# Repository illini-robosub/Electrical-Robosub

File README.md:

The RoboSub PCB components 

For now just power distribution board

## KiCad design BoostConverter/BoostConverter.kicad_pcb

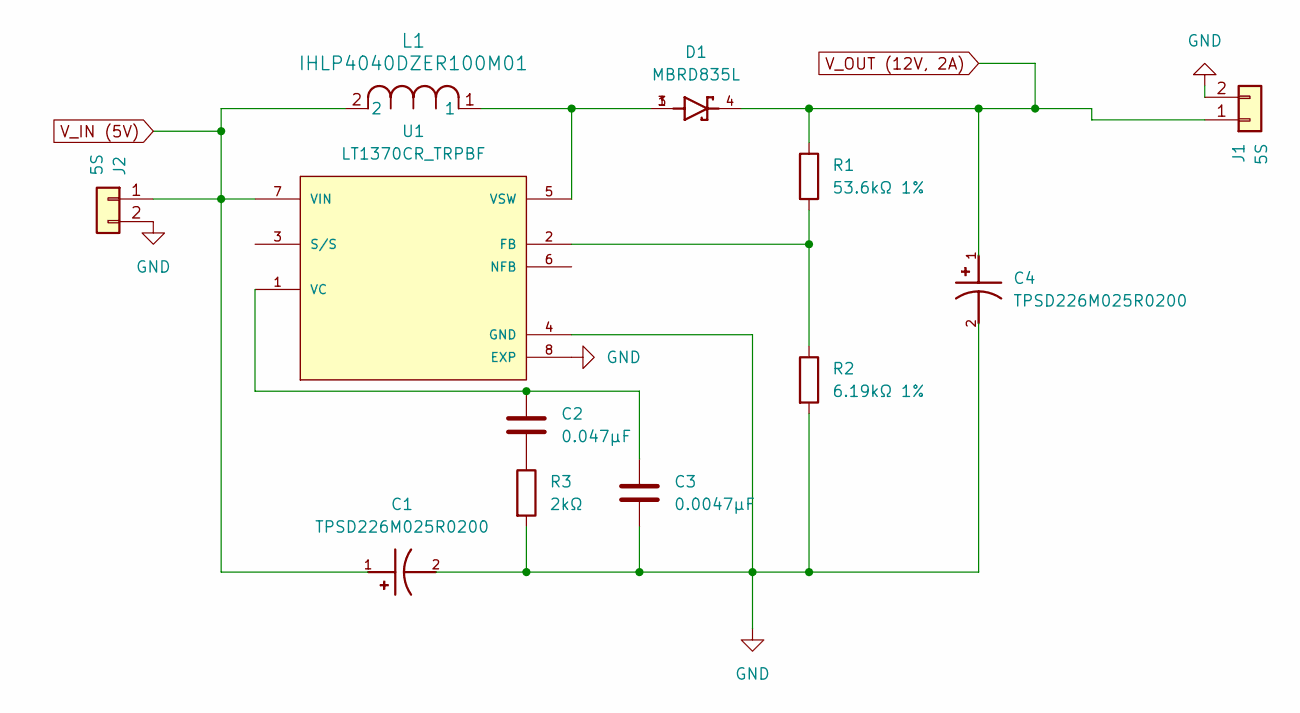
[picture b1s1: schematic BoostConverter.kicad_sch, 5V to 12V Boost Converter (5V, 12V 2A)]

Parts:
C1, C4: TPSD226M025R0200; CP_EIA-7343-30_AVX-N; PARTREV N/A
C2: 0.047µF; C_0603_1608Metric
C3: 0.0047µF; C_0603_1608Metric
D1: MBRD835L; TO-252-3_TabPin4; PARTREV 8
J1, J2: 5S; TerminalBlock_MetzConnect_Type086_RT03403HBLC_1x03_P3.81mm_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
L1: IHLP4040DZER100M01; L_Vishay_IHLP-4040
R1: 53.6kΩ 1%; R_0603_1608Metric
R2: 6.19kΩ 1%; R_0603_1608Metric
R3: 2kΩ; R_0603_1608Metric
U1: LT1370CR_TRPBF; TO-263-7_TabPin8

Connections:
GND: C1.2, C3.2, C4.2, J1.2, J2.2, R2.2, R3.2, U1.4 (GND), U1.8 (EXP)
unnamed: C2.2, R3.1
unnamed: R1.2, R2.1, U1.2 (FB)
unnamed: C2.1, C3.1, U1.1 (VC)
unnamed: D1.1, D1.3, L1.1, U1.5 (VSW)
V_IN (5V): C1.1, J2.1, L1.2, U1.7 (VIN)
V_OUT (12V, 2A): C4.1, D1.2, D1.4, J1.1, R1.1

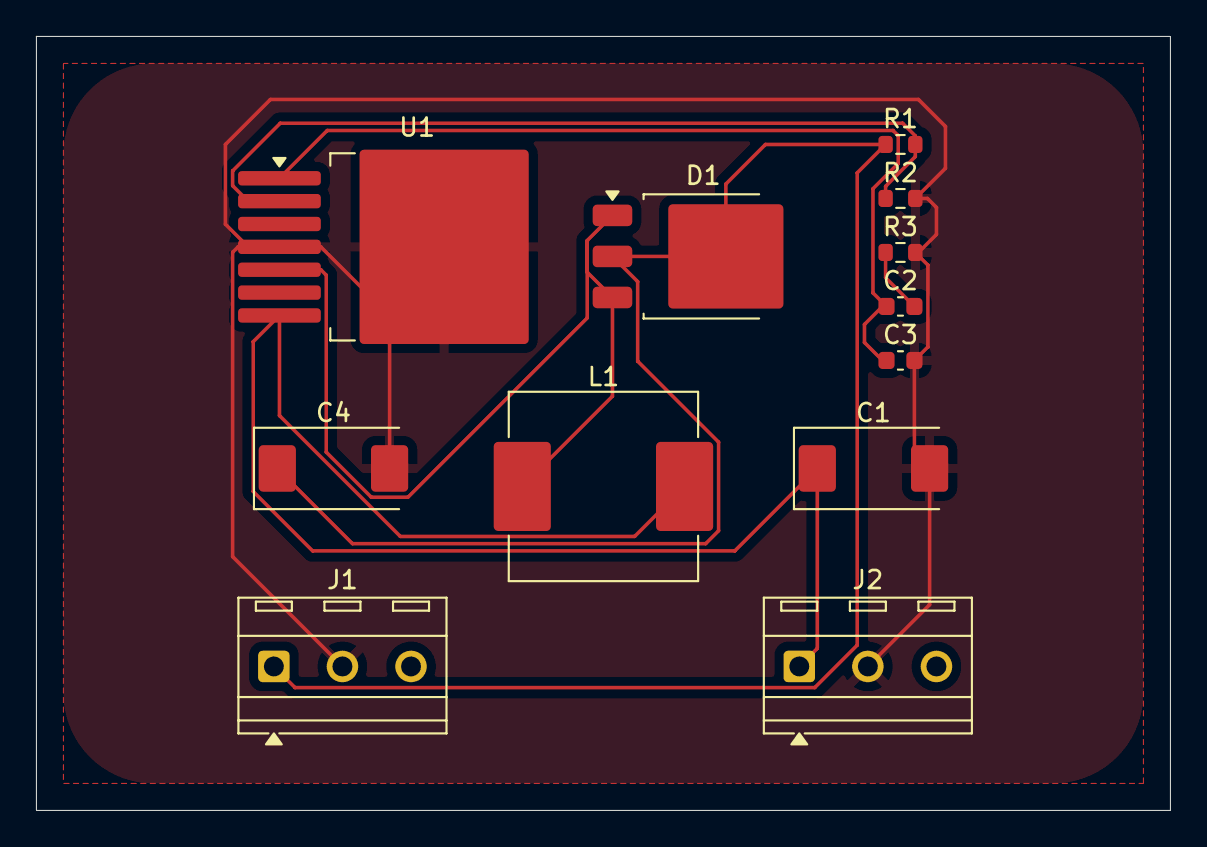
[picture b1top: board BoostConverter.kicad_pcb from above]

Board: 2 copper layers, 63.0 x 43.0 mm, 12 parts (0 on the bottom side), 7 nets.

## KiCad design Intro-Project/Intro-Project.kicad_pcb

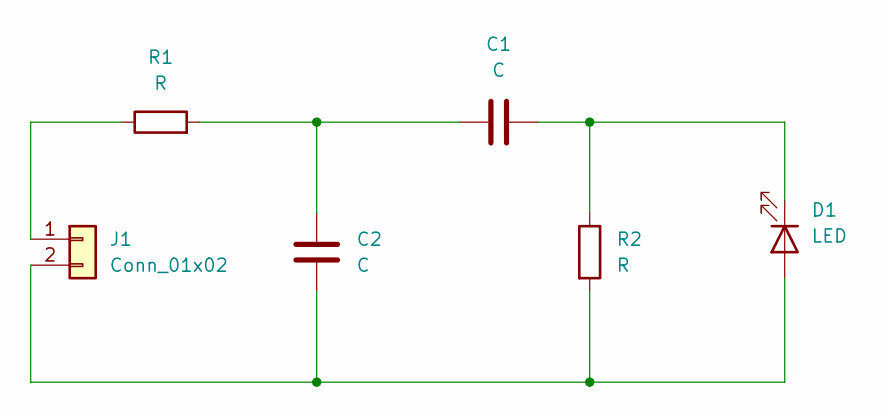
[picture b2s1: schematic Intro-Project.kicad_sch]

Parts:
C1, C2: C; CP_Axial_L10.0mm_D4.5mm_P15.00mm_Horizontal
D1: LED; LED_SLR-56_ROM
J1: Conn_01x02; BNC_Amphenol_031-5539_Vertical
R1, R2: R; R_Axial_DIN0204_L3.6mm_D1.6mm_P1.90mm_Vertical

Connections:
unnamed: C1.1, C2.1, R1.2
unnamed: C2.2, D1.2 (A), J1.2, R2.2
unnamed: C1.2, D1.1 (K), R2.1
unnamed: J1.1, R1.1

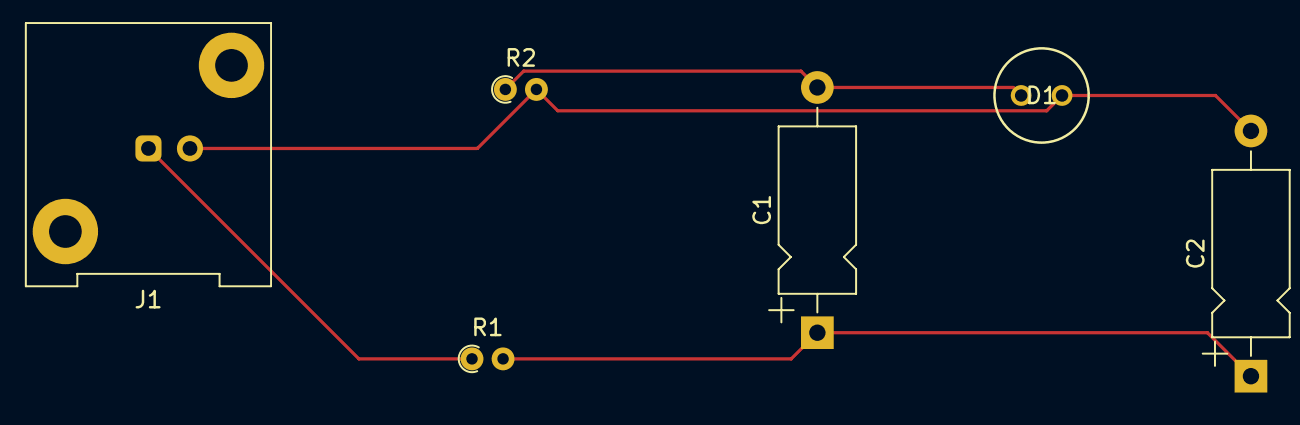
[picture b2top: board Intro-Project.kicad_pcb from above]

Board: 2 copper layers, 6 parts (0 on the bottom side), 4 nets.

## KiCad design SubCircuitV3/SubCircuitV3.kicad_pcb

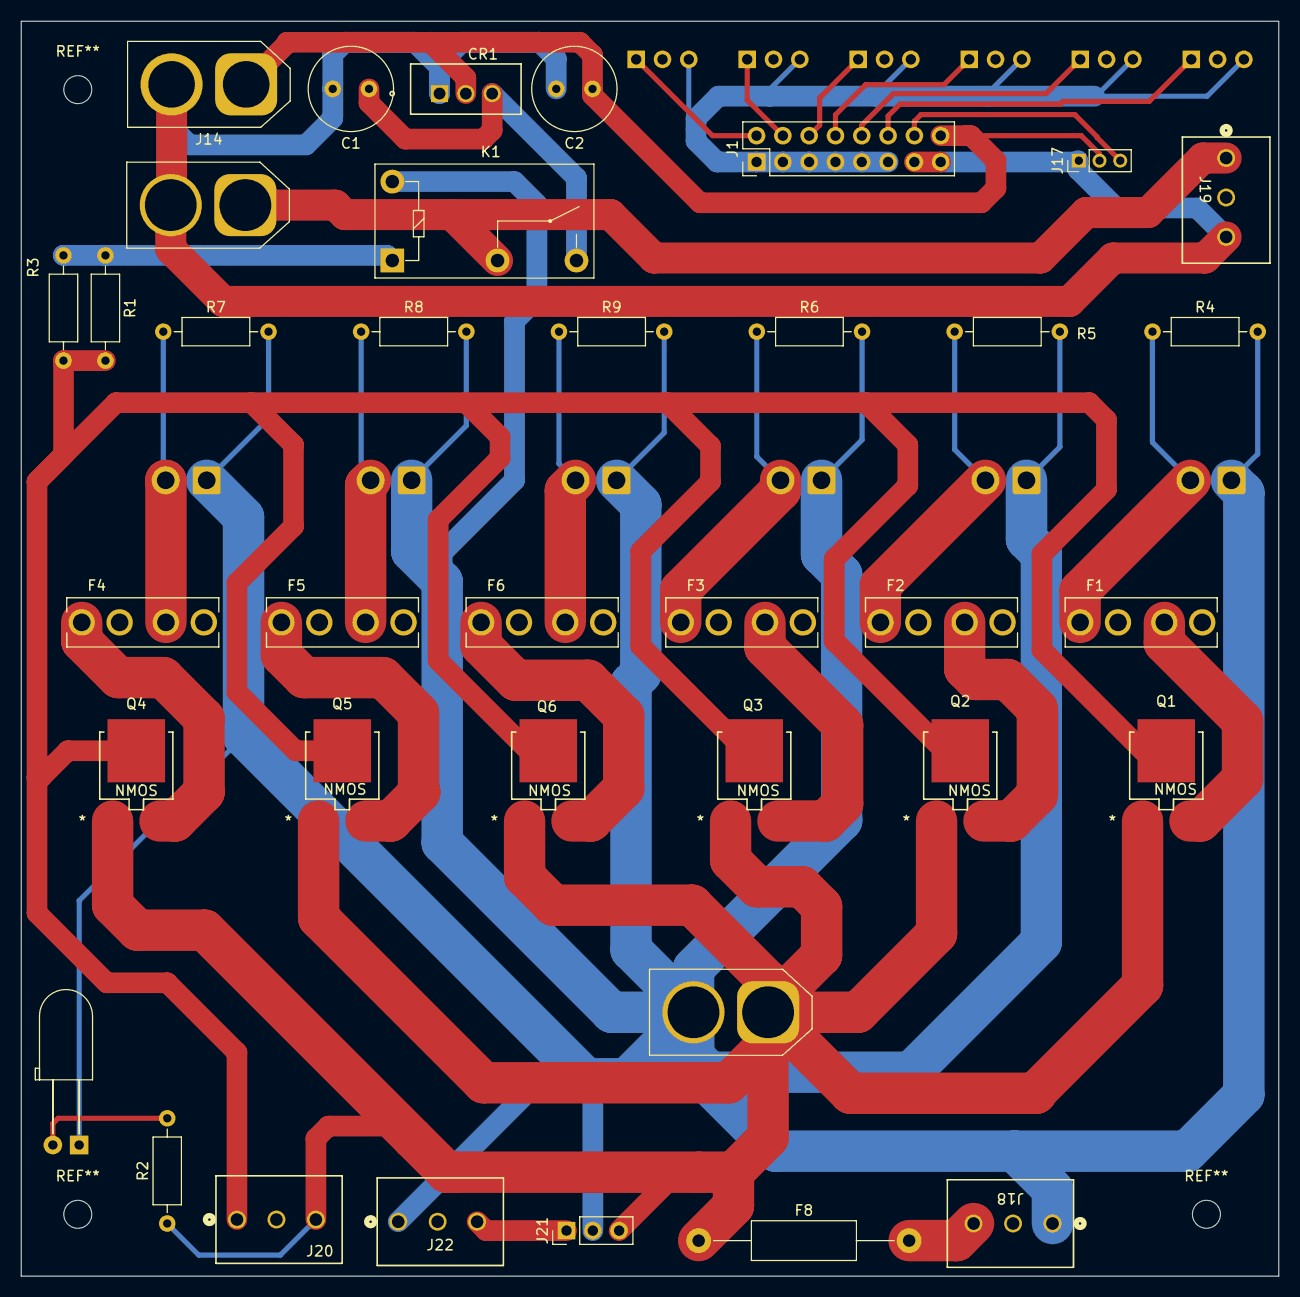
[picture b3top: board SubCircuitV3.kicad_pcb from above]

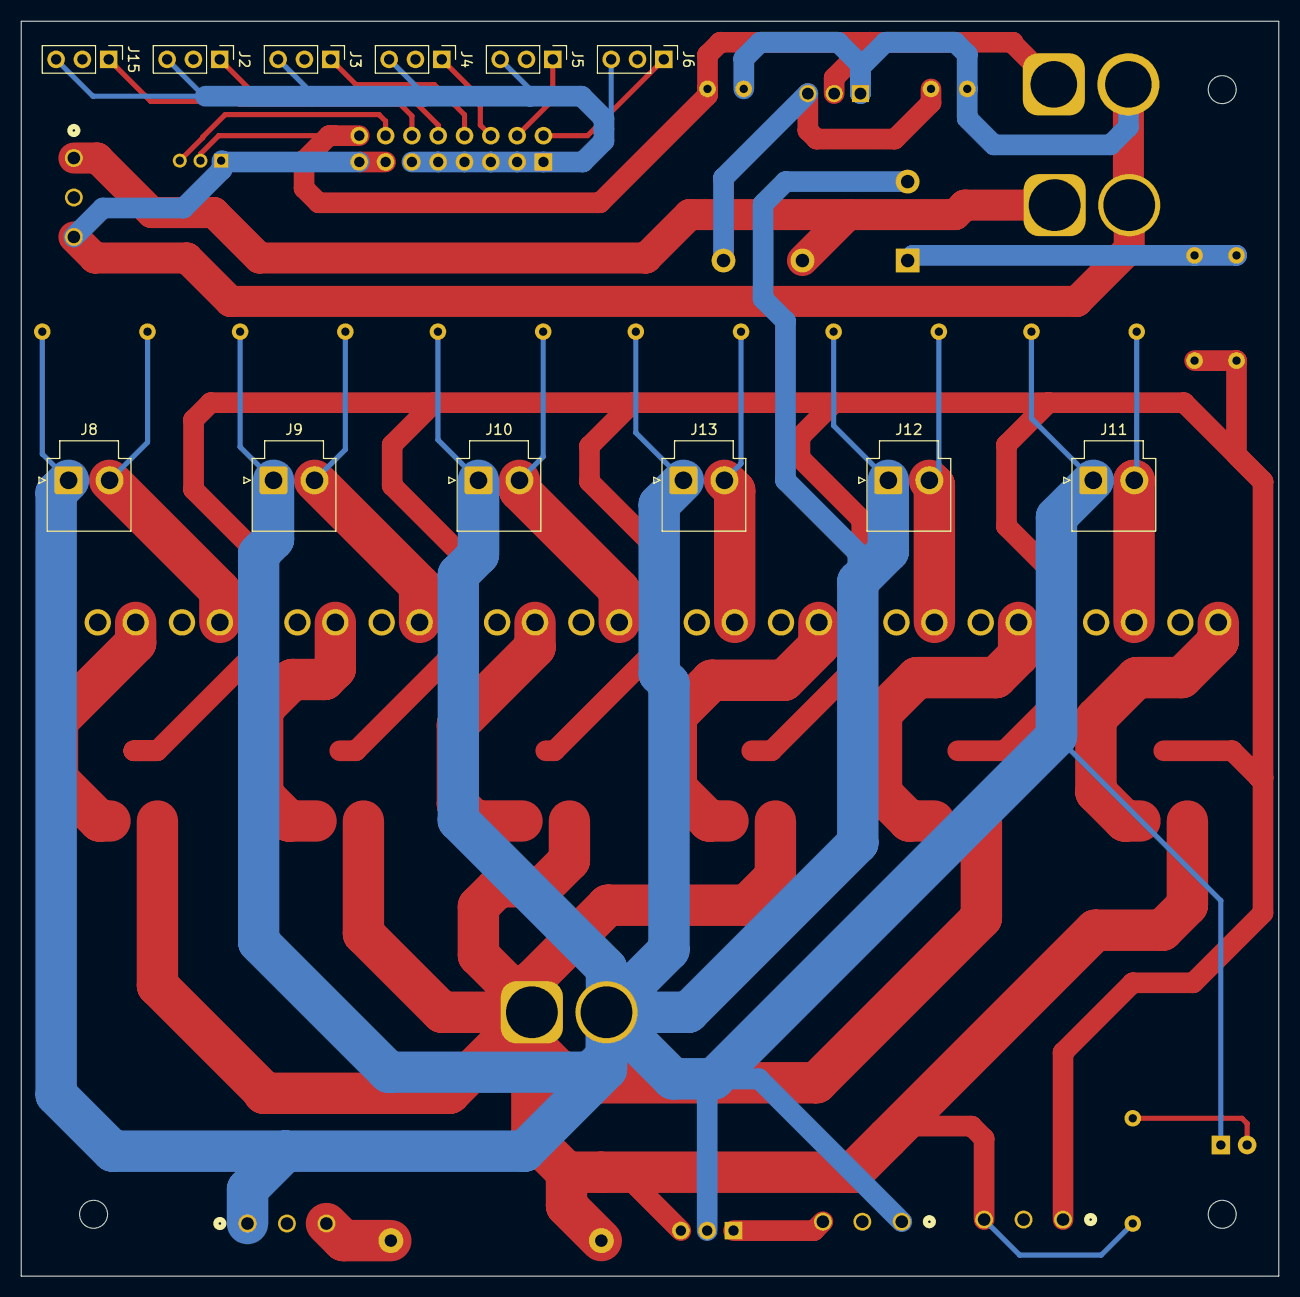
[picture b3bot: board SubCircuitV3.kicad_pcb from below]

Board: 2 copper layers, 121.4 x 121.2 mm, 49 parts (12 on the bottom side), 31 nets.

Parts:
C1, C2: 10u; C_Radial_D8.0mm_H7.0mm_P3.50mm
CR1: LD1085V50; TO-220_STM
D1: LED; LED_D5.0mm_Horizontal_O6.35mm_Z9.0mm
F1, F2, F3, F4, F5, F6: 3544-2; FUSE_3544-2
F8: Fuse; R_Axial_DIN0411_L9.9mm_D3.6mm_P20.32mm_Horizontal
J1: JTAG; PinHeader_2x08_P2.54mm_Vertical
J2, J3, J4, J5, J6, J15: ESC PWM; PinHeader_1x03_P2.54mm_Vertical
J7: 3S; XT90
J8, J9, J10, J11, J12, J13: ESC_POWER; JST_VH_B2P-VH-B_1x02_P3.96mm_Vertical
J14: FEMALE XT-60; AMASS_XT60-F_1x02_P7.20mm_Vertical
J16: 5S; XT90
J17: Water Sensor Input; PinHeader_1x03_P2.00mm_Vertical
J18: 3S OUT; CONN3_284392-3_TEC
J19: 2S OUT; CONN3_284392-3_TEC
J20: SWITCH; CONN3_284392-3_TEC
J21: U3V16F15; PinHeader_1x03_P2.54mm_Vertical
J22: CAM OUT; CONN3_284392-3_TEC
K1: G5Q-1A; Relay_SPST_Omron-G5Q-1A
Q1, Q2, Q3, Q4, Q5, Q6: NMOS; AOD454A
R1, R2, R3: 1000; R_Axial_DIN0207_L6.3mm_D2.5mm_P10.16mm_Horizontal
R4, R5, R6, R7, R8, R9: R; R_Axial_DIN0207_L6.3mm_D2.5mm_P10.16mm_Horizontal

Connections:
+7.5V: J7.1, J19.1, K1.2
+12V: F8.1, J16.1, J20.3, J21.3, Q1.1 (D), Q2.1 (D), Q3.1 (D), Q4.1 (D), Q5.1 (D), Q6.1 (D), R2.1
/SG: J20.1, Q1.2 (G), Q2.2 (G), Q3.2 (G), Q4.2 (G), Q5.2 (G), Q6.2 (G), R1.2, R3.2
GND1: D1.1 (K), J8.1, J9.1, J10.1, J11.1, J12.1, J13.1, J16.2, J18.1, J21.2, J22.1, K1.5, R4.2, R5.2, R6.2, R7.2, R8.2, R9.2
GND2: C1.2, C2.2, CR1.1 (ADJ/GND), J1.13, J1.15, J7.2, J14.2, J17.1, J19.3
GNDS: J1.1, J1.3, J1.5, J1.7, J1.9, J1.11, J2.3, J3.3, J4.3, J5.3, J6.3, J15.3
unnamed: C1.1, CR1.3 (INPUT), K1.3
unnamed: C2.1, CR1.2 (OUTPUT), J1.16, J14.1, J17.2
unnamed: D1.2 (A), R2.2
unnamed: J1.2, J6.1
unnamed: J1.4, J5.1
unnamed: J1.6, J4.1
unnamed: J1.8, J3.1
unnamed: J1.10, J2.1
unnamed: J1.12, J15.1
unnamed: J1.14, J17.3
unnamed: F1.1_1, J8.2, R4.1
unnamed: F2.1_1, J9.2, R5.1
unnamed: F3.1_1, J10.2, R6.1
unnamed: F4.2_1, J11.2, R7.1
unnamed: F5.2_1, J12.2, R8.1
unnamed: F6.2_1, J13.2, R9.1
unnamed: F8.2, J18.3
unnamed: J21.1, J22.3
unnamed: K1.1, R1.1, R3.1
unnamed: F1.2_1, Q1.3 (S)
unnamed: F2.2_1, Q2.3 (S)
unnamed: F3.2_1, Q3.3 (S)
unnamed: F4.1_1, Q4.3 (S)
unnamed: F5.1_1, Q5.3 (S)
unnamed: F6.1_1, Q6.3 (S)

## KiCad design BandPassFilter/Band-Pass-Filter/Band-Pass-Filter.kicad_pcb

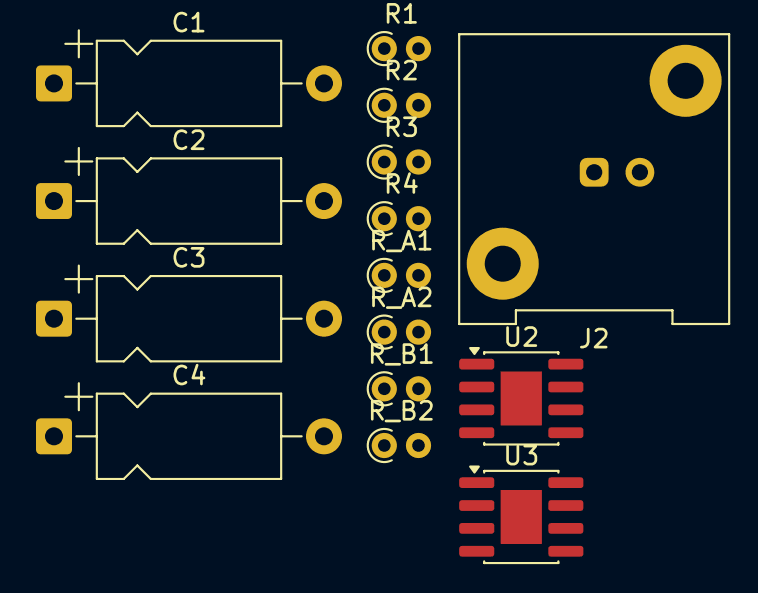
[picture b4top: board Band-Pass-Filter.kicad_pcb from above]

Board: 2 copper layers, 15 parts (0 on the bottom side), 9 nets, no tracks yet.

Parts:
C1, C2: 3nF; CP_Axial_L10.0mm_D4.5mm_P15.00mm_Horizontal
C3, C4: 6nF; CP_Axial_L10.0mm_D4.5mm_P15.00mm_Horizontal
J2: Conn_01x02; BNC_Amphenol_031-5539_Vertical
R1, R2, R3, R4: 10kΩ; R_Axial_DIN0204_L3.6mm_D1.6mm_P1.90mm_Vertical
R_A1, R_A2: R; R_Axial_DIN0204_L3.6mm_D1.6mm_P1.90mm_Vertical
R_B1, R_B2: R; R_Axial_DIN0204_L3.6mm_D1.6mm_P1.90mm_Vertical
U2, U3: SOIC-8-1EP_3.9x4.9mm_P1.27mm_EP2.29x3mm

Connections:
GND: J2.1, R4.2, R_B1.2, R_B2.2, U2.4 (V-), U3.4 (V-)
unnamed: C3.2, R_A1.1, U2.5
unnamed: R1.1, R2.1
unnamed: C4.2, R3.2
unnamed: R2.2, U2.1 (+)
unnamed: R_B1.1, U2.2 (-)
unnamed: R4.1, U3.1 (+)
unnamed: R_B2.1, U3.2 (-)
VOUT: R_A2.1, U3.5

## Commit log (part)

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2024-09-20 Initial Sub Circuit
2025-03-04 Finalized V3 Board
2025-03-13 Added water sensors and fixed JTAG-Capacitor connection error
2025-03-13 Killswitch and MOSFET implementation
2025-03-13 Fixed custom footprint assignments
2025-03-25 Updated footprint libraries
2025-03-25 Added mosfet
2025-04-03 Added fuses, mosfets, and updated power ports
2025-04-16 xt90 new footprint
2025-04-16 Update pin header and xt90 footprintg
2025-04-17 Larger routing wires
2025-04-29 Version 4
2025-09-23 removed F7 fuse
2025-09-23 Changed PWM Connectors
2025-09-30 Replaced old connectors with XT-60s
2025-10-02 Fixed spacing on rightmost XT-60
2025-10-04 Moved wire slightly up to avoid proximity error
2025-10-04 Updated library sync
2025-10-04 Fixed to meet design requirements
2025-10-04 Replaced male with female connectors
2025-10-04 Removed extra fuse
2025-10-04 Updated 2s output connections mismatch between PCB and Schematic
2025-10-04 newfuse
2025-10-05 Rearranged PCB layout to make room for boost convertor
2025-10-07 Added changes
2025-10-08 Replaced old boost convertor with U3V70F15
2025-10-13 Adjusted spacing
2025-10-13 Updated WaterSensor pin size
2026-02-03 Added Band Pass PCB
2026-02-03 some initial schema stuff
2026-02-10 second commit
2026-03-03 Initial Commit: Added Schematics for 5V to 12V (2A) Boost Converter
2026-03-31 Expanded hydrophone board
2026-03-31 LVDS_footpring
2026-03-31 Re-did layout for Boost Converter
2026-04-14 Updated capacitor/resistor values for Band Pass Filter
2026-04-21 added footprint for LVDS and added pins for esp
2026-04-21 completed_board
2026-04-25 Added Schematics for Input Filter

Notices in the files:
parts and their libraries:
Copyright 2016 Accelerated Designs. All rights reserved.
